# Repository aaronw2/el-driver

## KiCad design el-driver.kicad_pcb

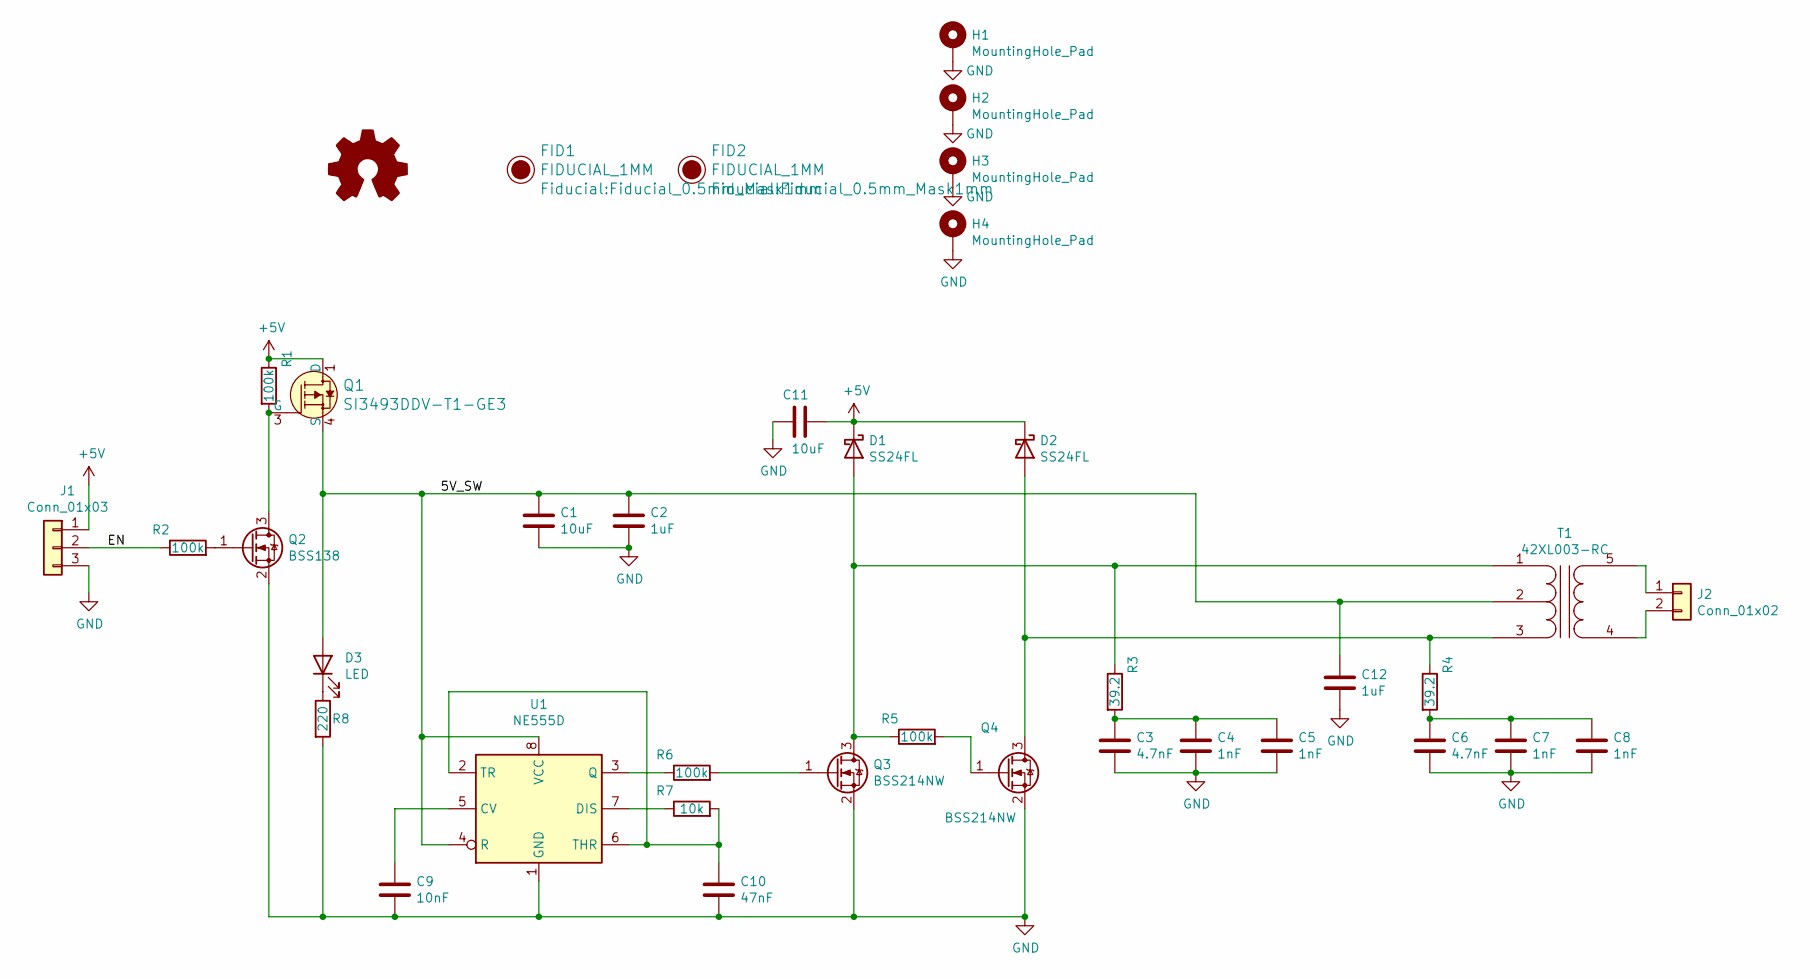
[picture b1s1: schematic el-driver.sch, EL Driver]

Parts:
C1, C11: 10uF; C_0603_1608Metric; MPN GRT188R61E106ME13D
C2, C12: 1uF; C_0603_1608Metric; MPN CL10B105KP8NNNC
C3, C6: 4.7nF; C_0603_1608Metric; MPN CL10B472KB8NNNC
C4, C5, C7, C8: 1nF; C_0603_1608Metric; MPN CL10B103KB8NNNC
C9: 10nF; C_0603_1608Metric; MPN CL10B103KB8NNNC
C10: 47nF; C_0603_1608Metric
D1, D2: SS24FL; D_SOD-123; MPN SS24FL
D3: LED; LED_0603_1608Metric; MPN 150060GS55040
FID1, FID2: FIDUCIAL_1MM; Fiducial_0.5mm_Mask1mm
H1, H2, H3, H4: MountingHole_Pad; MountingHole_2.2mm_M2_ISO7380_Pad
J1: Conn_01x03; JST_PH_B3B-PH-K_1x03_P2.00mm_Vertical; MPN B3B-PH-K-S(LF)(SN)
J2: Conn_01x02; JST_PH_B2B-PH-K_1x02_P2.00mm_Vertical; MPN B2B-PH-K-S(LF)(SN)
Q1: SI3493DDV-T1-GE3; SOT-23-6; MPN SI3493DDV-T1-GE3; Digi-Key_PN SI3493DDV-T1-GE3TR-ND
Q2: BSS138; SOT-23; MPN BSS138
Q3, Q4: BSS214NW; SOT-323_SC-70; MPN BSS214NWH6327XTSA1
R1, R2, R5, R6: 100k; R_0603_1608Metric; MPN CRG0603F100K
R3, R4: 39.2; R_0603_1608Metric; MPN RMCF0603FT39R2
R7: 10k; R_0603_1608Metric; MPN RK73H1JTTD1002F
R8: 220; R_0603_1608Metric; MPN RC0603FR-07220RL
T1: 42XL003-RC; Transformer_42XL_EI-14; MPN 42XL003-RC
U1: NE555D; SOIC-8_3.9x4.9mm_P1.27mm; MPN NE555D

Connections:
+5V: C11.1, D1.1 (K), D2.1 (K), J1.1, Q1.1 (D), Q1.2 (D), Q1.5 (D), Q1.6 (D), R1.1
/5V_SW: C1.1, C2.1, C12.1, D3.2 (A), Q1.4 (S), T1.2 (PM), U1.4 (R), U1.8 (VCC)
/EN: J1.2, R2.1
GND: C1.2, C2.2, C3.2, C4.2, C5.2, C6.2, C7.2, C8.2, C9.2, C10.2, C11.2, C12.2, H1.1, H2.1, H3.1, H4.1, J1.3, Q2.2 (S), Q3.2 (S), Q4.2 (S), R8.2, U1.1 (GND)
unnamed: C3.1, C4.1, C5.1, R3.2
unnamed: C6.1, C7.1, C8.1, R4.2
unnamed: C9.1, U1.5 (CV)
unnamed: C10.1, R7.2, U1.2 (TR), U1.6 (THR)
unnamed: D1.2 (A), Q3.3 (D), R3.1, R5.1, T1.1 (PR1)
unnamed: D2.2 (A), Q4.3 (D), R4.1, T1.3 (PR2)
unnamed: D3.1 (K), R8.1
unnamed: J2.1, T1.5 (S2)
unnamed: J2.2, T1.4 (S1)
unnamed: Q1.3 (G), Q2.3 (D), R1.2
unnamed: Q2.1 (G), R2.2
unnamed: Q3.1 (G), R6.2
unnamed: Q4.1 (G), R5.2
unnamed: R6.1, U1.3 (Q)
unnamed: R7.1, U1.7 (DIS)

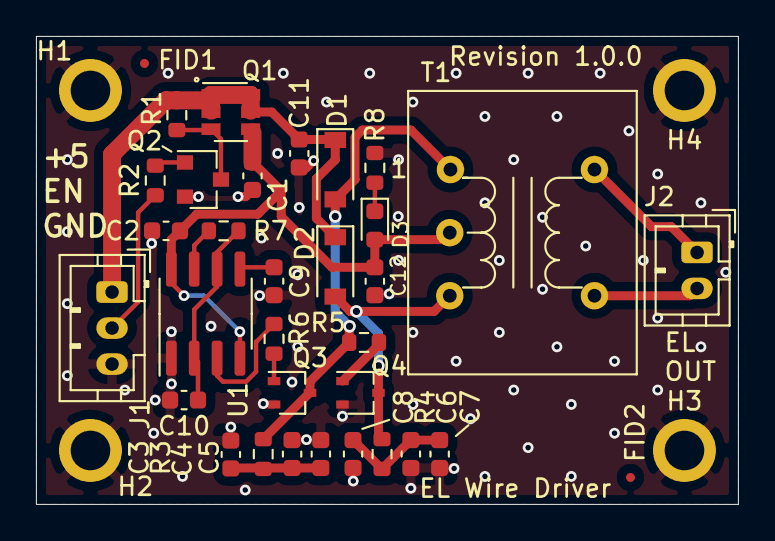
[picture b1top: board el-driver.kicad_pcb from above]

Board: 2 copper layers, 39.0 x 26.0 mm, 37 parts (0 on the bottom side), 19 nets.

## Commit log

2020-12-26 Initial checkin
2020-12-26 Version 2.0.0

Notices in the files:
el-driver.kicad_pcb:
Copyright © 2020 Aaron Williams
